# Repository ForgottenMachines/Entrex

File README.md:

# Entrex
Entrex is an early 1970s data entry systems, designed to replace punchcard data entry into larger mainframe computers.

The technologies documented here will include all like-kind systems manufactured by Nixdorf, Redifon, ROCC & Mera, all originally designed by Entrex Inc, Burlington, MA USA.

See See http://entrex480.com for greater details.

Enjoy!

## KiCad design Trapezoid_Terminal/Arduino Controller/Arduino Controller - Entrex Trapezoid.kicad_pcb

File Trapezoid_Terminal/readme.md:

WARNING:  Until refined & corrected, Global Label tag arrows may not indicate the 
proper signal in/out direction.
IN was used as default when KiCad Symbols (components) were not clear on 
In vs Out signals, so always check component datasheets when in doubt.

Crude Schematic Intro/Training Video (with lots of chapters for skipping):
https://www.youtube.com/watch?v=paqGd3PHxyc

Terminal/System use overview:
https://entrex480.blogspot.com/2022/09/how-does-entrexnixdorf-trapezoid.html

TucsonTom Collaborator Commentary:
http://cholla.mmto.org/computers/reverse/entrex/

EPROM Reverse Engineering:
https://github.com/phar/nixdorf-6xx-project

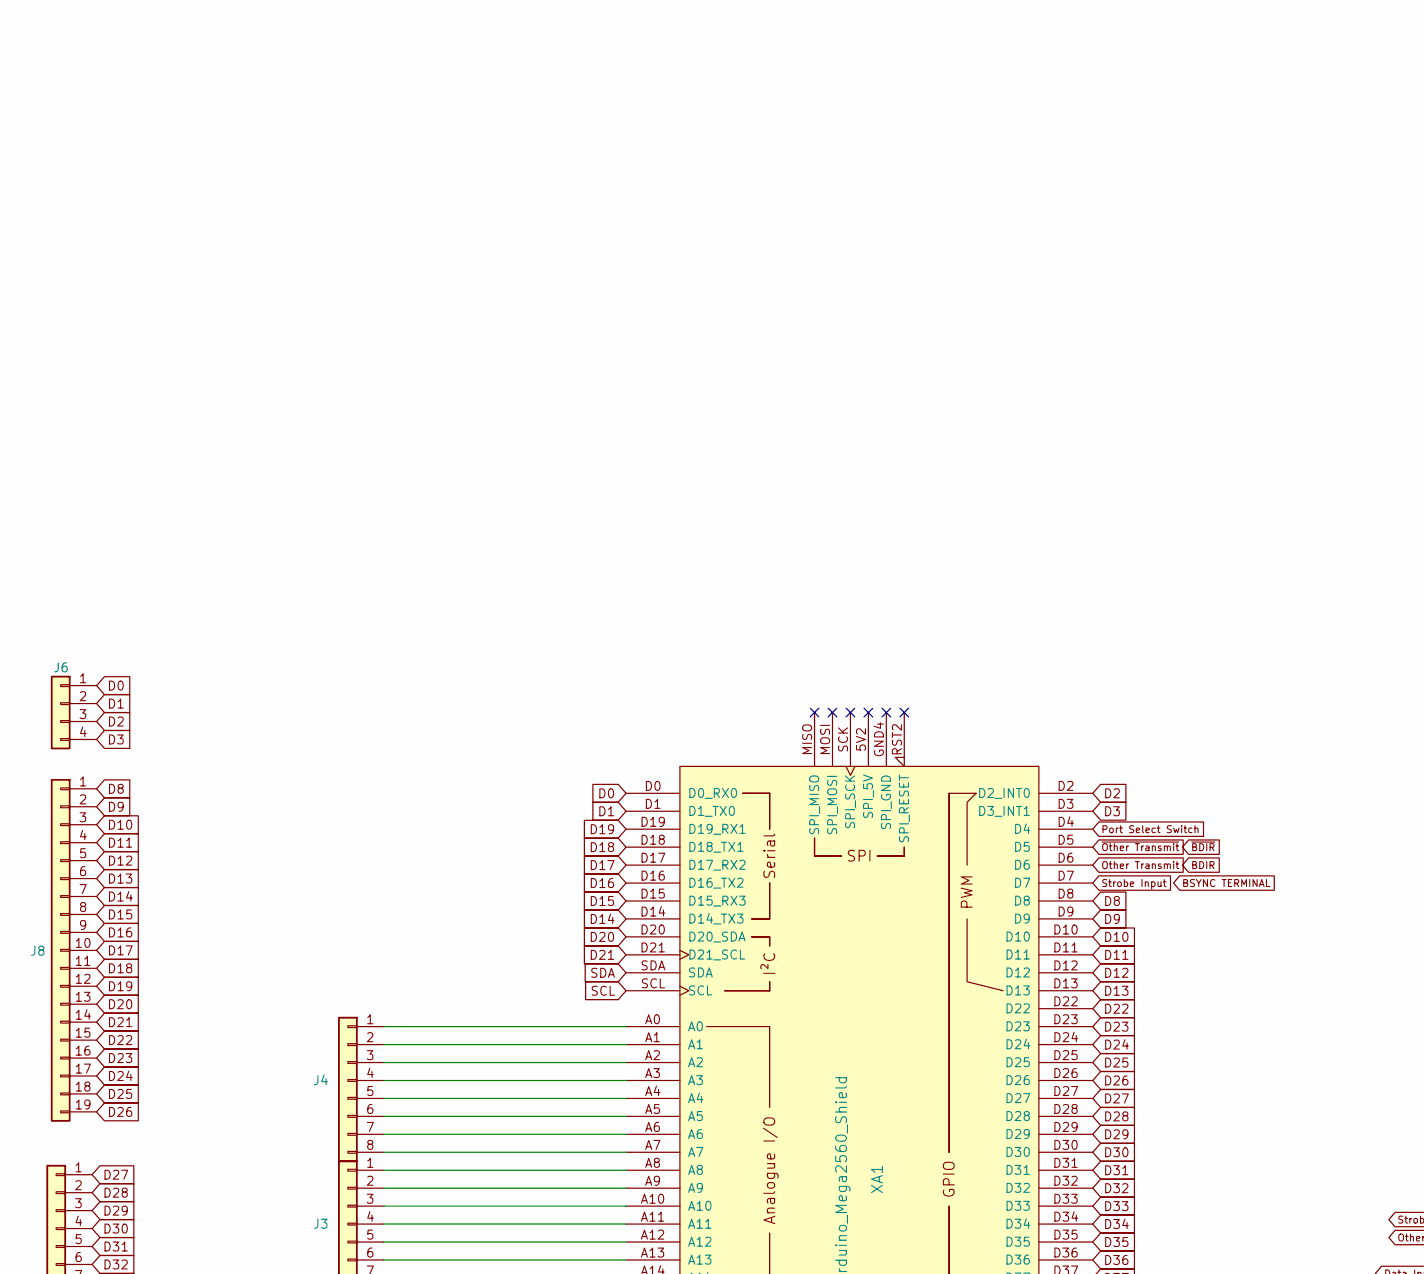
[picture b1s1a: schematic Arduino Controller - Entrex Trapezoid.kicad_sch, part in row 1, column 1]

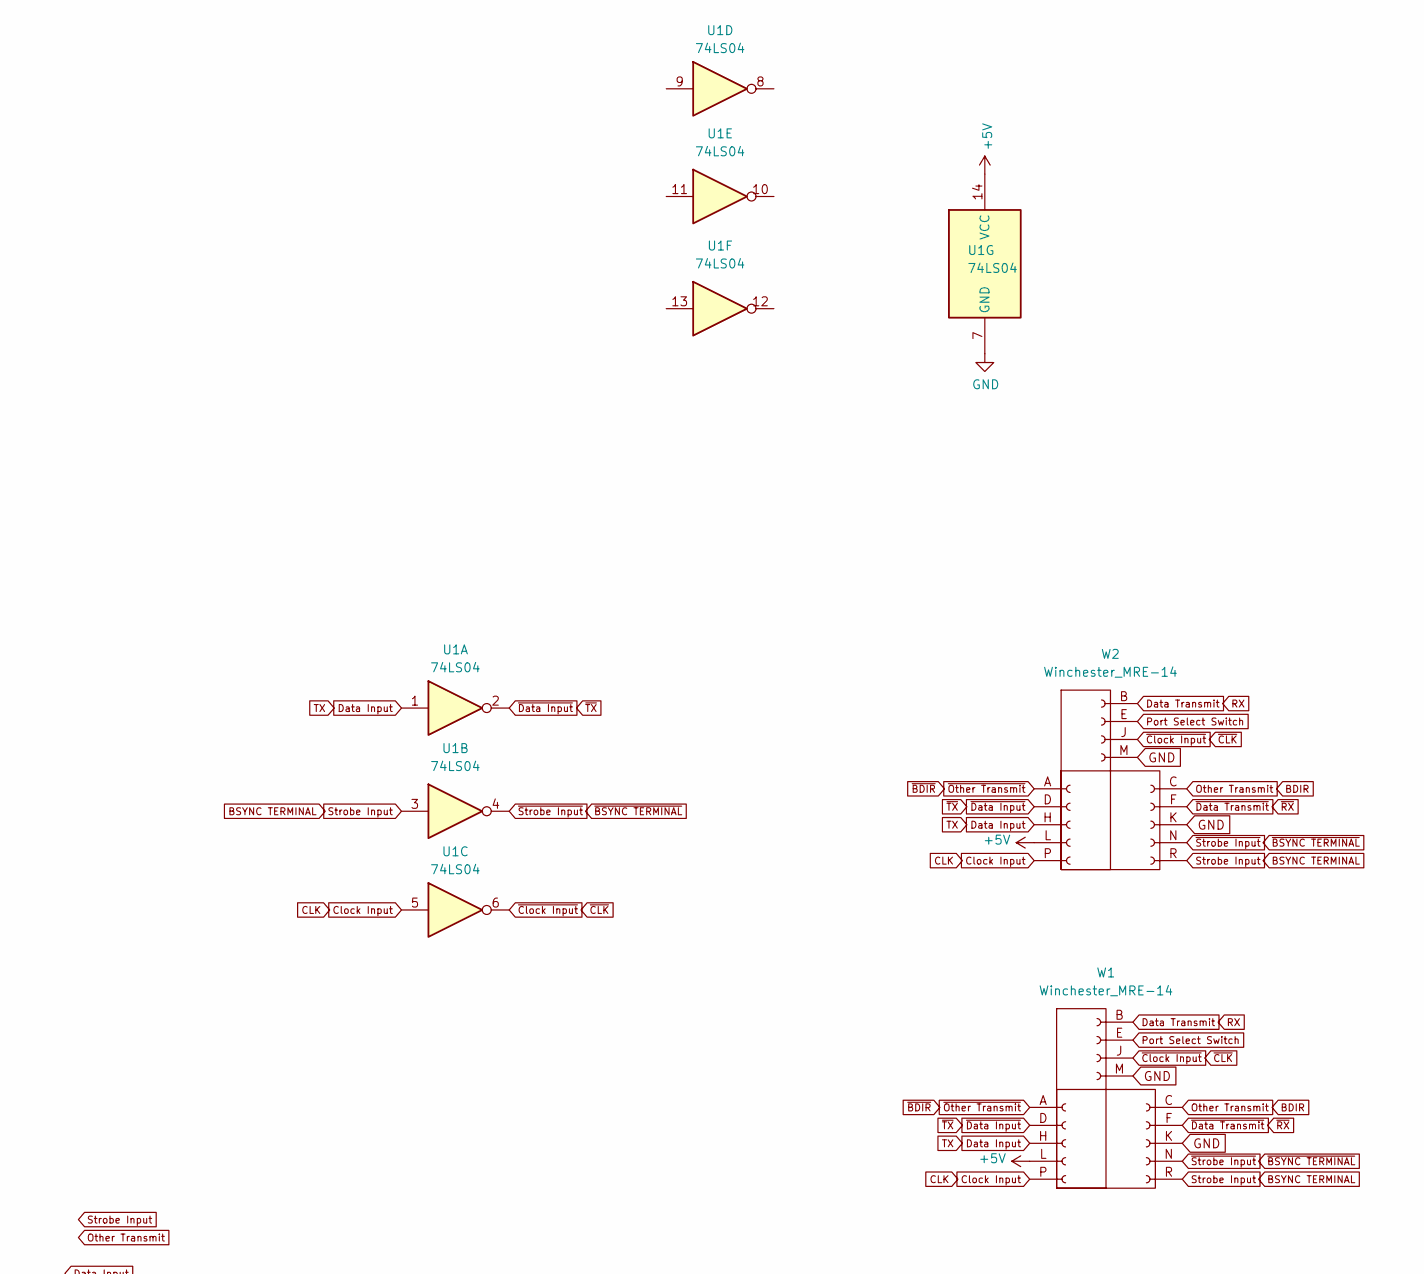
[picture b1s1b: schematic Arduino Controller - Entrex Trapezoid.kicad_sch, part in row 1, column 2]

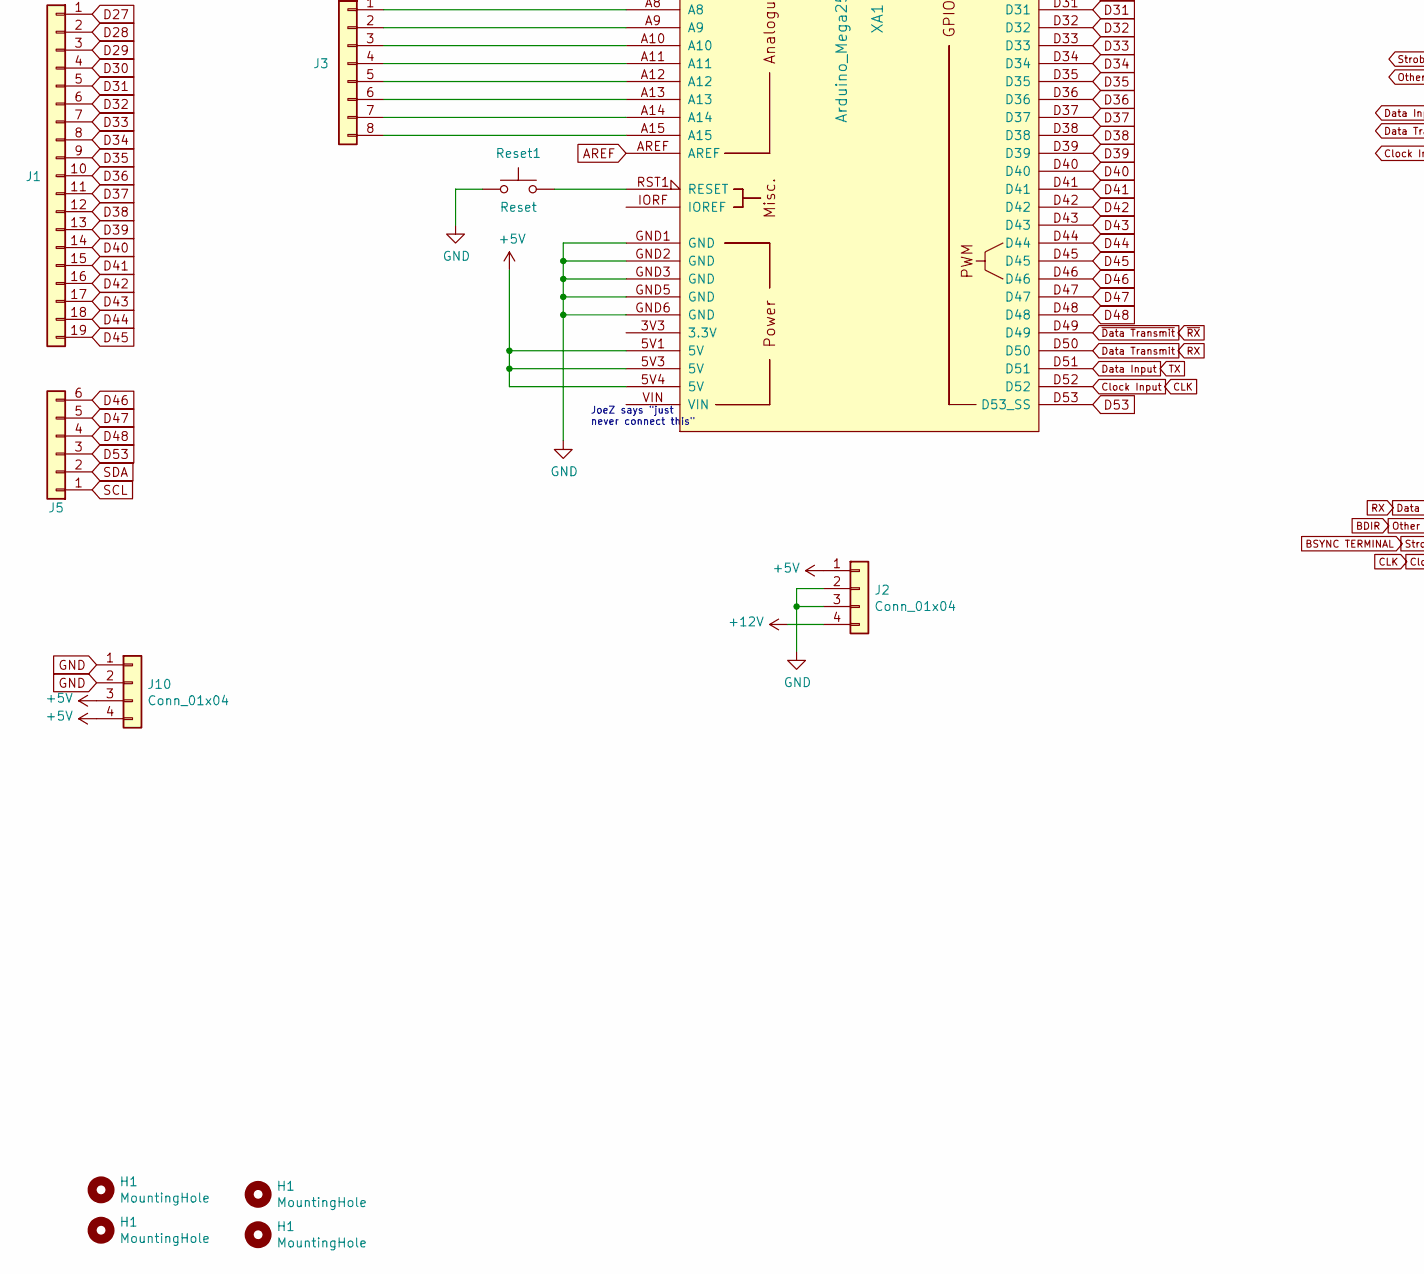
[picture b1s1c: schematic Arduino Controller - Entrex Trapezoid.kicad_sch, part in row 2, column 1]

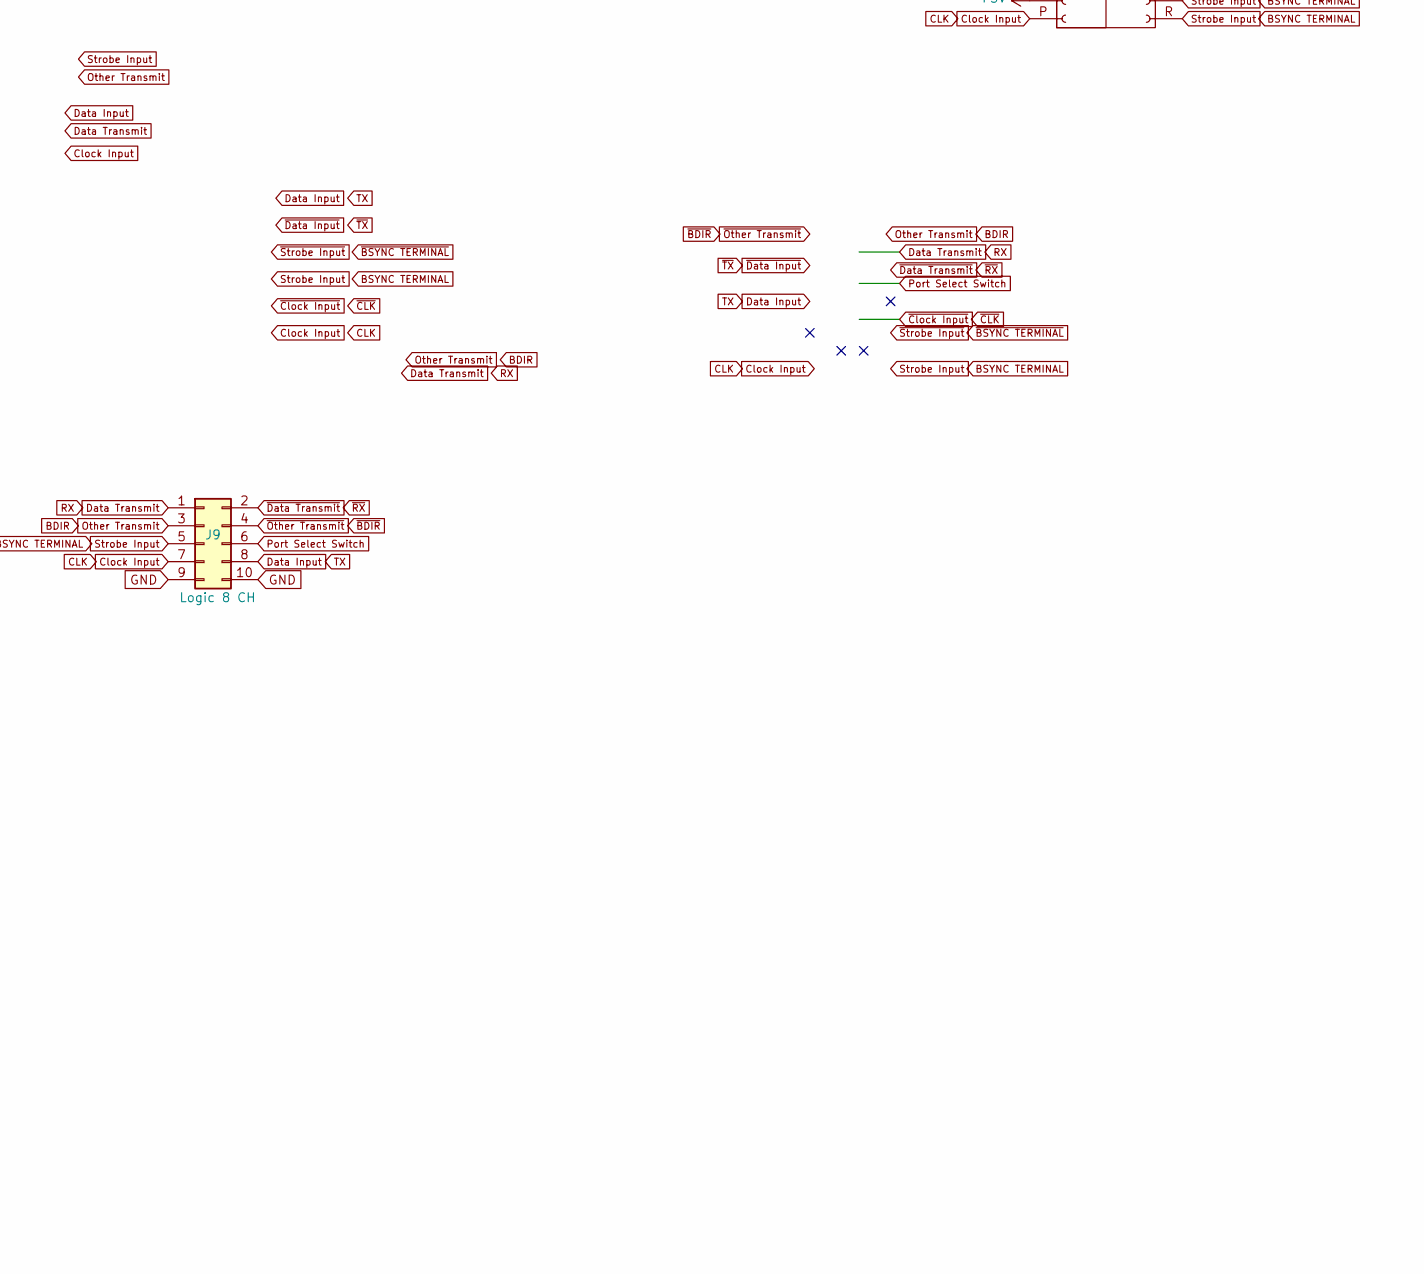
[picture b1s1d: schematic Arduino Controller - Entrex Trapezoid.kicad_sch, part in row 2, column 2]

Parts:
H1: MountingHole; MountingHole_3mm
J1, J8: Conn_01x19; PinHeader_1x19_P2.54mm_Vertical
J2, J6, J10: Conn_01x04; PinHeader_1x04_P2.54mm_Vertical
J3, J4: Conn_01x08; PinHeader_1x08_P2.54mm_Vertical
J5: Conn_01x06; PinHeader_1x06_P2.54mm_Vertical
J9: Logic 8 CH; PinHeader_2x05_P2.54mm_Vertical - Backside
Reset1: Reset; SW_PUSH_6mm
U1: 74LS04; DIP-14_W7.62mm
W1, W2: Winchester_MRE-14; Winchester MRE14 @ 2.54mm pitch
XA1: Arduino_Mega2560_Shield

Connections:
+5V: J2.1, J10.3, J10.4, U1.14 (VCC), W1.L (Pin_4), W2.L (Pin_4), XA1.5V1 (5V), XA1.5V3 (5V), XA1.5V4 (5V)
+12V: J2.4
AREF: XA1.AREF
Clock Input: J9.7, U1.5, W1.P (Pin_5), W2.P (Pin_5), XA1.D52
D0: J6.1, XA1.D0 (D0_RX0)
D1: J6.2, XA1.D1 (D1_TX0)
D2: J6.3, XA1.D2 (D2_INT0)
D3: J6.4, XA1.D3 (D3_INT1)
D8: J8.1, XA1.D8
D9: J8.2, XA1.D9
D10: J8.3, XA1.D10
D11: J8.4, XA1.D11
D12: J8.5, XA1.D12
D13: J8.6, XA1.D13
D14: J8.7, XA1.D14 (D14_TX3)
D15: J8.8, XA1.D15 (D15_RX3)
D16: J8.9, XA1.D16 (D16_TX2)
D17: J8.10, XA1.D17 (D17_RX2)
D18: J8.11, XA1.D18 (D18_TX1)
D19: J8.12, XA1.D19 (D19_RX1)
D20: J8.13, XA1.D20 (D20_SDA)
D21: J8.14, XA1.D21 (D21_SCL)
D22: J8.15, XA1.D22
D23: J8.16, XA1.D23
D24: J8.17, XA1.D24
D25: J8.18, XA1.D25
D26: J8.19, XA1.D26
D27: J1.1, XA1.D27
D28: J1.2, XA1.D28
D29: J1.3, XA1.D29
D30: J1.4, XA1.D30
D31: J1.5, XA1.D31
D32: J1.6, XA1.D32
D33: J1.7, XA1.D33
D34: J1.8, XA1.D34
D35: J1.9, XA1.D35
D36: J1.10, XA1.D36
D37: J1.11, XA1.D37
D38: J1.12, XA1.D38
D39: J1.13, XA1.D39
D40: J1.14, XA1.D40
D41: J1.15, XA1.D41
D42: J1.16, XA1.D42
D43: J1.17, XA1.D43
D44: J1.18, XA1.D44
D45: J1.19, XA1.D45
D46: J5.6, XA1.D46
D47: J5.5, XA1.D47
D48: J5.4, XA1.D48
D53: J5.3, XA1.D53 (D53_SS)
Data Input: J9.8, U1.1, W1.H (Pin_3), W2.H (Pin_3), XA1.D51
Data Transmit: J9.1, W1.B (Pin_4), W2.B (Pin_4), XA1.D50
GND: J2.2, J2.3, J9.9, J9.10, J10.1, J10.2, Reset1.1, U1.7 (GND), W1.K (Pin_3), W1.M (Pin_1), W2.K (Pin_3), W2.M (Pin_1), XA1.GND1 (GND), XA1.GND2 (GND), XA1.GND3 (GND), XA1.GND5 (GND), XA1.GND6 (GND)
unnamed: J3.1, XA1.A8
unnamed: J3.2, XA1.A9
unnamed: J3.3, XA1.A10
unnamed: J3.4, XA1.A11
unnamed: J3.5, XA1.A12
unnamed: J3.6, XA1.A13
unnamed: J3.7, XA1.A14
unnamed: J3.8, XA1.A15
unnamed: J4.1, XA1.A0
unnamed: J4.2, XA1.A1
unnamed: J4.3, XA1.A2
unnamed: J4.4, XA1.A3
unnamed: J4.5, XA1.A4
unnamed: J4.6, XA1.A5
unnamed: J4.7, XA1.A6
unnamed: J4.8, XA1.A7
unnamed: Reset1.2, XA1.RST1 (RESET)
Other Transmit: J9.3, W1.C (Pin_5), W2.C (Pin_5), XA1.D6
Port Select Switch: J9.6, W1.E (Pin_3), W2.E (Pin_3), XA1.D4
SCL: J5.1, XA1.SCL
SDA: J5.2, XA1.SDA
~Clock Input: U1.6, W1.J (Pin_2), W2.J (Pin_2)
~Data Input: U1.2, W1.D (Pin_2), W2.D (Pin_2)
~Data Transmit: J9.2, W1.F (Pin_4), W2.F (Pin_4), XA1.D49
~Other Transmit: J9.4, W1.A (Pin_1), W2.A (Pin_1), XA1.D5

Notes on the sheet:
JoeZ says "just never connect this"

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
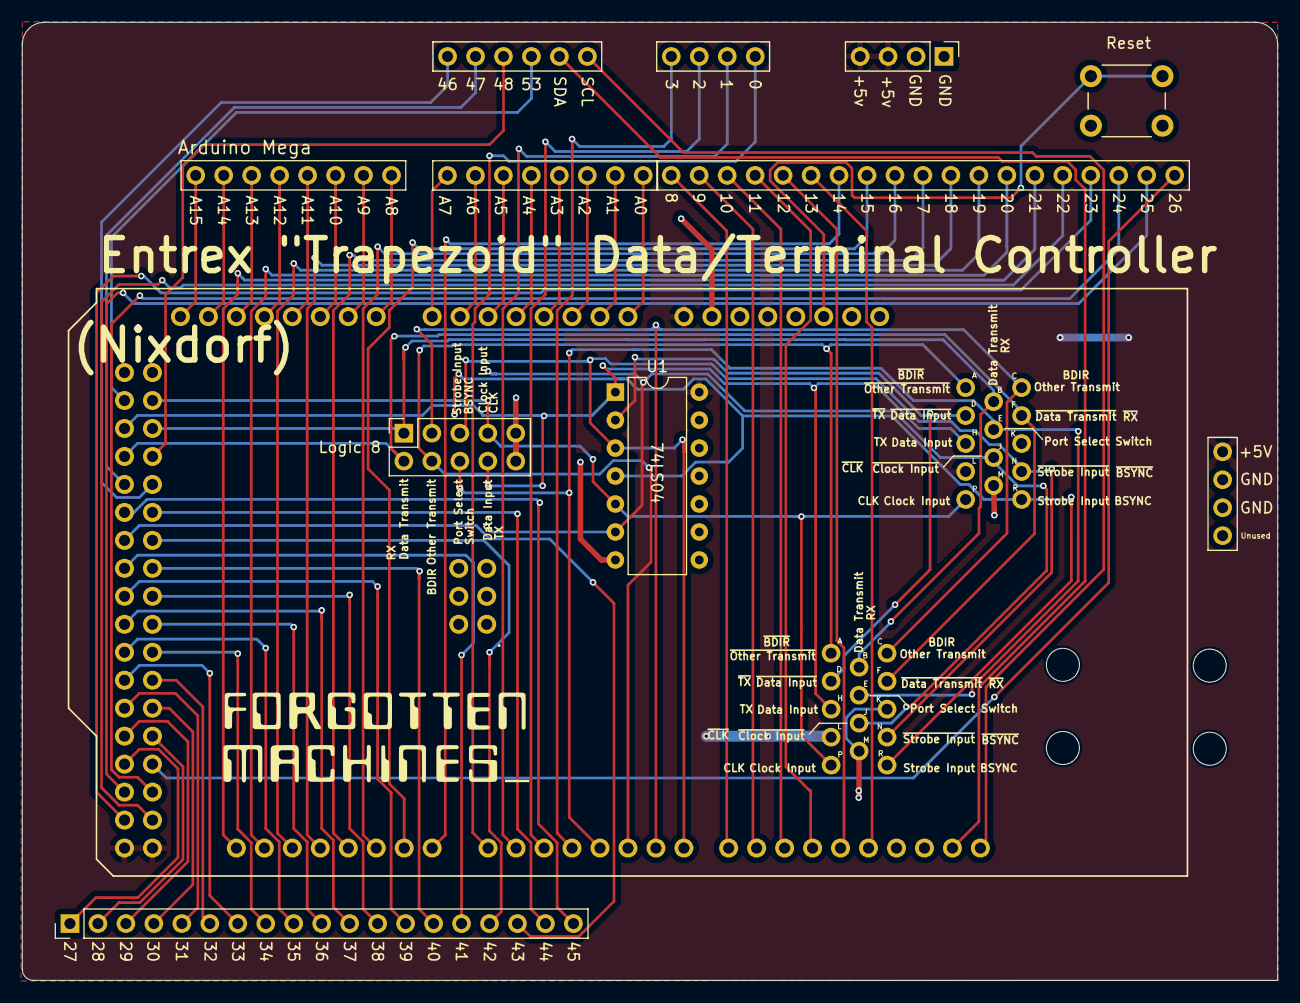
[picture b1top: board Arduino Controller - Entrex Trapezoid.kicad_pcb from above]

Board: 2 copper layers, 114.0 x 87.0 mm, 18 parts (0 on the bottom side), 78 nets.

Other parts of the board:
H2, H3, H4: MountingHole; MountingHole_3mm

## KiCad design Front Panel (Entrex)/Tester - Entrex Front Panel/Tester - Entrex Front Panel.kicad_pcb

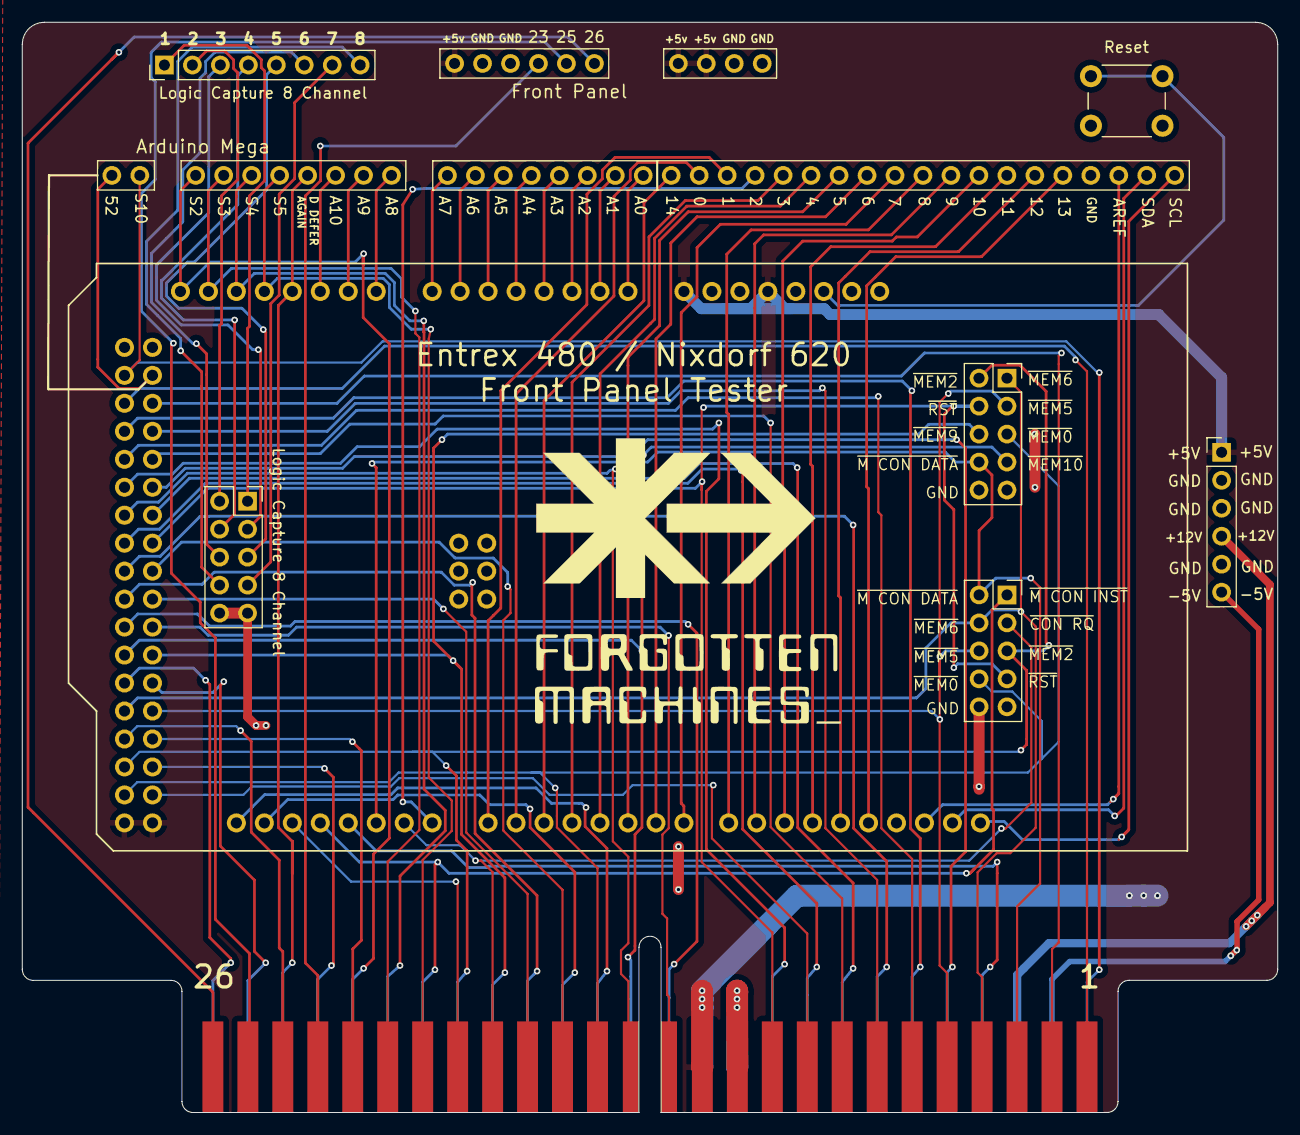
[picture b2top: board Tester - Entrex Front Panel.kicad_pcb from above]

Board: 2 copper layers, 114.0 x 99.0 mm, 14 parts (1 on the bottom side), 89 nets.

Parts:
J1: Logic 8 CH; PinHeader_1x08_P2.54mm_Vertical
J2: Conn_01x04; PinHeader_1x06_P2.54mm_Vertical
J3, J4: Conn_01x08; PinHeader_1x08_P2.54mm_Vertical
J5: Conn_01x06; PinHeader_1x06_P2.54mm_Vertical
J6: Conn_01x04; PinHeader_1x04_P2.54mm_Vertical
J7: Conn_01x02; PinHeader_1x02_P2.54mm_Vertical
J8: Conn_01x19; PinHeader_1x19_P2.54mm_Vertical
J9, J11, J12: Logic 8 CH; PinHeader_2x05_P2.54mm_Vertical - Backside
J10: Conn_02x26_Top_Bottom; DG Nova Front Panel Card Edge
SW1: Reset; SW_PUSH_6mm
XA1: Arduino_Mega2560_Shield

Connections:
52: J10.52, XA1.D31
64K: J10.42, XA1.D20 (D20_SDA)
+5V: J2.1, J5.6, J6.3, J6.4, J10.12, J10.38, XA1.5V1 (5V), XA1.5V3 (5V), XA1.5V4 (5V), XA1.VIN
+V LAMP: J2.4, J10.29
-5V: J2.6, J10.28
AREF: J8.17, XA1.AREF
D3: J8.5, XA1.D3 (D3_INT1)
D4: J8.6, XA1.D4
D5: J8.7, XA1.D5
D6: J8.8, XA1.D6
D7: J8.9, XA1.D7
D8: J8.10, XA1.D8
D9: J8.11, XA1.D9
D10: J8.12, XA1.D10
D11: J8.13, XA1.D11
D12: J8.14, XA1.D12
D13: J8.15, XA1.D13
D DEFER AGAIN: J3.4, J10.50, XA1.A11
DISK CS: J10.6, XA1.D47
EXT CS: J10.32, XA1.D49
GND: J2.2, J2.3, J2.5, J5.4, J5.5, J6.1, J6.2, J8.16, J9.9, J9.10, J10.11, J10.37, J11.9, J11.10, J12.9, J12.10, SW1.1, XA1.GND1 (GND), XA1.GND2 (GND), XA1.GND3 (GND), XA1.GND5 (GND), XA1.GND6 (GND)
Logic1: J1.1, J12.1
Logic2: J1.2, J12.2
Logic3: J1.3, J12.3
Logic4: J1.4, J12.4
Logic5: J1.5, J12.5
Logic6: J1.6, J12.6
Logic7: J1.7, J12.7
Logic8: J1.8, J12.8
unnamed: J3.1, XA1.A8
unnamed: J3.2, XA1.A9
unnamed: J3.3, XA1.A10
unnamed: J4.1, XA1.A0
unnamed: J4.2, XA1.A1
unnamed: J4.3, XA1.A2
unnamed: J4.4, XA1.A3
unnamed: J4.5, XA1.A4
unnamed: J4.6, XA1.A5
unnamed: J4.7, XA1.A6
unnamed: J4.8, XA1.A7
unnamed: J7.1, XA1.D52
unnamed: J8.1, XA1.D2 (D2_INT0)
unnamed: J8.2, XA1.D1 (D1_TX0)
unnamed: J8.3, XA1.D0 (D0_RX0)
unnamed: J8.4, XA1.D14 (D14_TX3)
unnamed: J5.3, J10.23
unnamed: J5.2, J10.25
unnamed: J5.1, J10.26
unnamed: SW1.2, XA1.RST1 (RESET)
S2: J3.8, J10.48, XA1.A15
S3: J3.7, J10.21, XA1.A14
S4: J3.6, J10.47, XA1.A13
S5: J3.5, J10.20, XA1.A12
S10: J7.2, J10.27, XA1.D53 (D53_SS)
SCL: J8.19, XA1.SCL
SDA: J8.18, XA1.SDA
SWITCHOVER POWER: J10.2, XA1.D50
TAPE CS: J10.7, XA1.D48
~64K: J10.41, XA1.D21 (D21_SCL)
~CON DATA: J10.30, XA1.D17 (D17_RX2)
~CON INST: J10.19, XA1.D19 (D19_RX1)
~CON RQ: J10.18, J11.3, XA1.D15 (D15_RX3)
~DCHP OUT: J10.14, XA1.D43
~DEFER: J10.35, XA1.D41
~DISK RDY: J10.8, XA1.D46
~M CON DATA: J9.8, J10.3, J11.2, XA1.D16 (D16_TX2)
~M CON INST: J10.46, J11.1, XA1.D18 (D18_TX1)
~MA LOAD: J10.34, XA1.D42
~MBO0: J10.9, XA1.D22
~MEM0: J9.5, J10.15, J11.8, XA1.D23
~MEM1: J10.49, XA1.D24
~MEM2: J9.2, J10.45, J11.5, XA1.D25
~MEM3: J10.22, XA1.D26
~MEM4: J10.24, XA1.D27
~MEM5: J9.3, J10.5, J11.6, XA1.D28
~MEM6: J9.1, J10.4, J11.4, XA1.D29
~MEM7: J10.51, XA1.D30
~MEM9: J9.6, J10.44, XA1.D32
~MEM10: J9.7, J10.40, XA1.D33
~MEM11: J10.13, XA1.D34
~MEM12: J10.39, XA1.D35
~MEM13: J10.17, XA1.D36
~MEM14: J10.43, XA1.D37
~MEM15: J10.16, XA1.D38
~NORMAL: J10.1, XA1.D51
~POWER FAIL: J10.31, XA1.D44
~RST: J9.4, J10.10, J11.7, XA1.D40
~RUN: J10.33, XA1.D39
~SCNR BUSY: J10.36, XA1.D45

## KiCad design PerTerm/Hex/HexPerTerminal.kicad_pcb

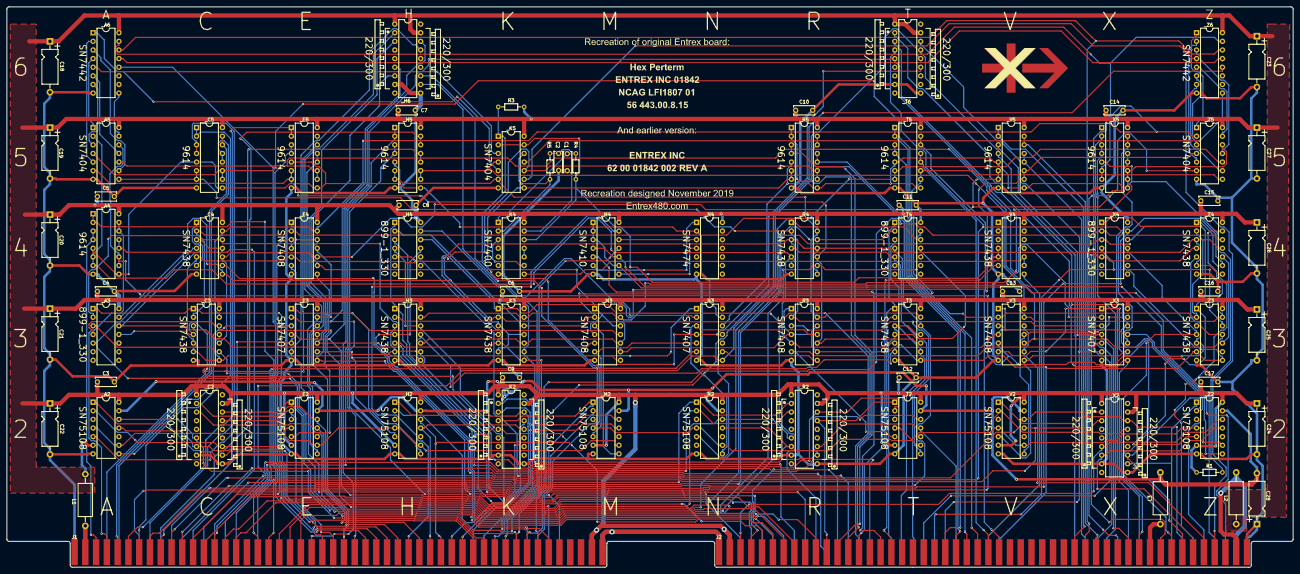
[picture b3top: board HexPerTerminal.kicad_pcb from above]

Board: 2 copper layers, 379.0 x 165.1 mm, 89 parts (0 on the bottom side), 194 nets.

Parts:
C1, C2: 470pF; C_Disc_D6.0mm_W2.5mm_P5.00mm
C3, C4, C5, C6, C7, C8, C9, C10, C11, C12, C13, C14, C15, C16, C17: 0.05uF; C_Disc_D6.0mm_W2.5mm_P5.00mm
C18, C19, C20, C21, C22, C23, C24, C25, C26, C27, C28: 6.8uF; CP_Axial_L10.0mm_D4.5mm_P15.00mm_Horizontal
G1: LOGO; logoFullN
G2: LOGO; logoXN
J1: portA; portA_NovaMod
J2: portB; portB_NovaMod
L1, L2, L3: 10uH; L_Axial_L9.5mm_D4.0mm_P15.24mm_Horizontal_Fastron_SMCC
R1, R3: 1K; R_Axial_DIN0204_L3.6mm_D1.6mm_P7.62mm_Horizontal
R4, R5: 220; R_Axial_DIN0204_L3.6mm_D1.6mm_P7.62mm_Horizontal
_A2: SN75108; DIP-14_W7.62mm
_A3: 899-1_330; DIP-14_W7.62mm
_A4: 9614; DIP-16_W7.62mm
_A5: SN7404; DIP-14_W7.62mm
_A6: SN7442; DIP-16_W7.62mm
_C2: 899-5_R220_R330; DIP-18_dualRnetwork
_C3, _C4: SN7438; DIP-14_W7.62mm
_C5: 9614; DIP-16_W7.62mm
_E2: SN75108; DIP-14_W7.62mm
_E3: SN7407; DIP-14_W7.62mm
_E4: SN7408; DIP-14_W7.62mm
_E5: 9614; DIP-16_W7.62mm
_H2: SN75108; DIP-14_W7.62mm
_H3: SN7438; DIP-14_W7.62mm
_H4: 899-1_330; DIP-14_W7.62mm
_H5: 9614; DIP-16_W7.62mm
_H6: 899-5_R220_R330; DIP-18_dualRnetwork
_K2: 899-5_R220_R330; DIP-18_dualRnetwork
_K3: SN7438; DIP-14_W7.62mm
_K4: SN7400; DIP-14_W7.62mm
_K5: SN7404; DIP-14_W7.62mm
_M2: SN75108; DIP-14_W7.62mm
_M3: SN7408; DIP-14_W7.62mm
_M4: SN7410; DIP-14_W7.62mm
_N2: SN75108; DIP-14_W7.62mm
_N3: SN7407; DIP-14_W7.62mm
_N4: SN7474; DIP-14_W7.62mm
_R2: 899-5_R220_R330; DIP-18_dualRnetwork
_R3: SN7408; DIP-14_W7.62mm
_R4: SN7438; DIP-14_W7.62mm
_R5: 9614; DIP-16_W7.62mm
_T2: SN75108; DIP-14_W7.62mm
_T3: SN7438; DIP-14_W7.62mm
_T4: 899-1_330; DIP-14_W7.62mm
_T5: 9614; DIP-16_W7.62mm
_T6: 899-5_R220_R330; DIP-18_dualRnetwork
_V2: SN75108; DIP-14_W7.62mm
_V3: SN7408; DIP-14_W7.62mm
_V4: SN7438; DIP-14_W7.62mm
_V5: 9614; DIP-16_W7.62mm
_X2: 899-5_R220_R330; DIP-18_dualRnetwork
_X3: SN7407; DIP-14_W7.62mm
_X4: 899-1_330; DIP-14_W7.62mm
_X5: 9614; DIP-16_W7.62mm
_Z2: SN75108; DIP-14_W7.62mm
_Z3, _Z4: SN7438; DIP-14_W7.62mm
_Z5: SN7404; DIP-14_W7.62mm
_Z6: SN7442; DIP-16_W7.62mm

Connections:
+5V: C3.1, C4.1, C5.1, C6.1, C7.1, C8.1, C9.1, C10.1, C11.1, C12.1, C13.1, C14.1, C15.1, C16.1, C17.1, C18.1, C19.1, C20.1, C21.1, C22.1, C23.1, C24.1, C25.1, C26.1, C27.1, J1.97, J1.98, J2.3, J2.4, L1.2, L2.2, R1.1, R3.2, _A2.6, _A2.14, _A4.16, _A5.14, _A6.16, _C2.14, _C3.14, _C4.14, _C5.16, _E2.6, _E2.14, _E3.14, _E4.14, _E5.16, _H2.6, _H2.14, _H3.14, _H5.16, _H6.14, _K2.14, _K3.14, _K4.14, _K5.14, _M2.6, _M2.14, _M3.14, _M4.14, _N2.6, _N2.14, _N3.14, _N4.14, _R2.14, _R3.14, _R4.14, _R5.16, _T2.6, _T2.14, _T3.14, _T5.16, _T6.14, _V2.6, _V2.14, _V3.14, _V4.14, _V5.16, _X2.14, _X3.14, _X5.16, _Z2.6, _Z2.14, _Z3.14, _Z4.14, _Z5.14, _Z6.16
-5V: C28.2, L3.2, _A2.13, _E2.13, _H2.13, _M2.13, _N2.13, _T2.13, _V2.13, _Z2.13
/InputGates/InGateBlock1/OutCh1: _E2.8, _E3.13, _E4.11
/InputGates/InGateBlock1/OutCh2: _E2.5, _E3.11, _E4.8
/InputGates/InGateBlock1/OutCh3: _A2.8, _E3.3, _E4.3
/InputGates/InGateBlock1/OutCh4: _A2.5, _E3.5, _E4.6
/InputGates/InGateBlock1/OutDr: R3.1, _A2.4, _A2.9, _E2.4, _E2.9, _H2.4, _H2.9, _K5.1, _M2.4, _M2.9, _N2.4, _N2.9, _T2.4, _T2.9, _V2.4, _V2.9, _Z2.4, _Z2.9
/InputGates/InGateBlock2/OutCh1: _E3.1, _H2.8, _M3.11
/InputGates/InGateBlock2/OutCh2: _E3.9, _H2.5, _M3.8
/InputGates/InGateBlock2/OutCh3: _M2.8, _M3.3, _N3.1
/InputGates/InGateBlock2/OutCh4: _M2.5, _M3.6, _N3.5
/InputGates/InGateBlock3/OutCh1: _N2.8, _N3.3, _R3.11
/InputGates/InGateBlock3/OutCh2: _N2.5, _N3.9, _R3.8
/InputGates/InGateBlock3/OutCh3: _R3.3, _T2.8, _X3.3
/InputGates/InGateBlock3/OutCh4: _R3.6, _T2.5, _X3.5
/InputGates/InGateBlock4/OutCh1: _V2.8, _V3.11, _X3.13
/InputGates/InGateBlock4/OutCh2: _V2.5, _V3.8, _X3.9
/InputGates/InGateBlock4/OutCh3: _V3.3, _X3.11, _Z2.8
/InputGates/InGateBlock4/OutCh4: _V3.6, _X3.1, _Z2.5
/OutputDrives/DriversBlock1/InAdrv: R1.2, _N3.12, _R5.5, _R5.9, _T5.5, _T5.9, _V5.5, _V5.9, _X5.5, _X5.9
/OutputDrives/DriversBlock2/InAdrv: _A4.5, _A4.9, _C5.5, _C5.9, _E5.5, _E5.9, _H5.5, _H5.9, _N3.13, _N4.2, _N4.6
A3: J1.3, J1.4, L1.1
A5: J1.5, _A4.3, _A4.4
A7: J1.7, _A4.14, _A4.15
A8: J1.8, _E5.14, _E5.15
A9: J1.9, _C5.14, _C5.15
A10: J1.10, _C5.12, _C5.13
A11: J1.11, _E5.1, _E5.2
A13: J1.13, _C5.1, _C5.2
A14: J1.14, _X4.13, _Z4.9
A15: J1.15, _V2.2, _X2.12
A16: J1.16, _C5.3, _C5.4
A17: J1.17, _H5.14, _H5.15
A18: J1.18, _H5.12, _H5.13
A19: J1.19, _T6.3, _X3.10
A20: J1.20, _T3.12, _T4.4
A21: J1.21, _R4.12, _T4.2
A22: J1.22, _N2.2, _R2.2
A23: J1.23, _E5.3, _E5.4
A24: J1.24, _A4.12, _A4.13
A25: J1.25, _X4.3, _Z3.9
A26: J1.26, _N2.1, _R2.1
A27: J1.27, _N3.8, _T6.11
A28: J1.28, _V2.12, _X2.1
A29: J1.29, _N2.12, _R2.5
A30: J1.30, _R2.13, _T2.2
A31: J1.31, _R4.9, _T4.13
A32: J1.32, _H5.1, _H5.2
A35: J1.35, _N3.4, _T6.10
A36: J1.36, _V2.11, _X2.2
A37: J1.37, _A4.1, _A4.2
A39: J1.39, _R4.1, _T4.12
A41: J1.41, _N2.11, _R2.6
A43: J1.43, _X4.2, _Z4.12
A45: J1.45, _T6.4, _X3.2
A47: J1.47, _C2.12, _E2.2
A49: J1.49, _C2.13, _E2.1
A51: J1.51, _E5.12, _E5.13
A53: J1.53, _H5.3, _H5.4
A55: J1.55, _A6.12
A57: J1.57, _A2.2, _C2.9
A59: J1.59, _A2.1, _C2.8
A61: J1.61, _C2.1, _E2.12
A63: J1.63, _M4.13
A65: J1.65, _C2.2, _E2.11
A67: J1.67, _H2.11, _K2.11
A69: J1.69, _H2.12, _K2.10
A71: J1.71, _H2.2, _K2.12
A73: J1.73, _H2.1, _K2.13
A75: J1.75, _A2.11, _C2.6
A76: J1.76, _K2.2, _M2.11
A77: J1.77, _A2.12, _C2.5
A78: J1.78, _K2.1, _M2.12
A79: J1.79, _M4.11
A81: J1.81, _C4.3, _C4.6, _C4.8, _C4.11, _K3.3, _K3.6, _K3.8, _K3.11, _R4.3, _R4.6, _R4.8, _R4.11, _Z4.3, _Z4.6, _Z4.8, _Z4.11
A83: J1.83, _Z6.12
A84: J1.84, _E3.12, _H6.1
A85: J1.85, _K2.4, _M2.2
A86: J1.86, _E3.10, _H6.2
A87: J1.87, _K2.3, _M2.1
A88: J1.88, _H6.9, _N3.6
A89: J1.89, _H6.8, _N3.2
A90: J1.90, _E3.4, _H6.13
A92: J1.92, _E3.6, _H6.12
B5: J2.5, _X2.5, _Z2.12
B6: J2.6, _E3.8, _H6.6
B7: J2.7, _R2.8, _T2.12
B8: J2.8, _E3.2, _H6.5
B9: J2.9, _A3.1, _C3.1
B10: J2.10, _A3.11, _C3.4
B11: J2.11, _H3.1, _H4.1
B12: J2.12, _H3.4, _H4.11
B13: J2.13, _A3.4, _C3.12
B14: J2.14, _A3.3, _C3.9
B15: J2.15, _H3.12, _H4.4
B16: J2.16, _H3.9, _H4.3
B18: J2.18, _A3.12, _C4.1
B19: J2.19, _A3.5, _C4.4
B20: J2.20, _H4.12, _K3.1
B21: J2.21, _R2.12, _T2.1
B22: J2.22, _H4.5, _K3.4
B23: J2.23, _R5.3, _R5.4
B24: J2.24, _A3.2, _C4.12
B25: J2.25, _R5.1, _R5.2
B26: J2.26, _A3.13, _C4.9
B27: J2.27, _V4.6
B28: J2.28, _H4.2, _K3.12
B30: J2.30, _H4.13, _K3.9
B31: J2.31, _M4.5
B33: J2.33, _T3.1, _T4.1
B34: J2.34, _T3.4, _T4.11
B36: J2.36, _T3.9, _T4.3
B38: J2.38, _R4.4, _T4.5
B40: J2.40, _A6.15, _Z6.15
B42: J2.42, _X4.4, _Z3.12
B43: J2.43, _R5.12, _R5.13
B44: J2.44, _T6.13, _X3.6
B45: J2.45, _R5.14, _R5.15
B46: J2.46, _R2.9, _T2.11
B47: J2.47, _T5.3, _T5.4
B49: J2.49, _T5.1, _T5.2
B51: J2.51, _T5.12, _T5.13
B52: J2.52, _V4.8
B53: J2.53, _T5.14, _T5.15
B54: J2.54, _C3.3, _C3.6, _C3.8, _C3.11, _H3.3, _H3.6, _H3.8, _H3.11, _T3.3, _T3.6, _T3.8, _T3.11, _Z3.3, _Z3.6, _Z3.8, _Z3.11
B67: J2.67, _V5.1, _V5.2
B68: J2.68, _V5.3, _V5.4
B69: J2.69, _A6.14, _Z6.14
B70: J2.70, _V5.12, _V5.13
B71: J2.71, _V5.14, _V5.15
B72: J2.72, _X5.1, _X5.2
B74: J2.74, _X5.3, _X5.4
B76: J2.76, _X5.12, _X5.13
B77: J2.77, _T6.12, _X3.4
B78: J2.78, _X5.14, _X5.15
B79: J2.79, _X4.11, _Z3.4
B80: J2.80, _T6.2, _X3.8
B81: J2.81, L3.1
B83: J2.83, _X4.5, _Z4.4
B85: J2.85, _X4.1, _Z3.1
B86: J2.86, _X2.8, _Z2.1
B87: J2.87, _X2.9, _Z2.2
B88: J2.88, _V2.1, _X2.13
B89: J2.89, _X2.6, _Z2.11
B90: J2.90, _X4.12, _Z4.1
B91: J2.91, _E4.1, _E4.4, _E4.9, _E4.12, _M3.1, _M3.4, _M3.9, _M3.12, _R3.1, _R3.4, _R3.9, _R3.12, _V3.1, _V3.4, _V3.9, _V3.12
B92: J2.92, _T6.1, _X3.12
B93: J2.93, _A6.13, _Z6.13
B94: J2.94, _M4.1, _M4.2, _M4.3, _M4.9
B96: J2.96, _M4.4, _M4.10
B97: J2.97, J2.98, L2.1
GNDD: C1.2, C2.1, C3.2, C4.2, C5.2, C6.2, C7.2, C8.2, C9.2, C10.2, C11.2, C12.2, C13.2, C14.2, C15.2, C16.2, C17.2, C18.2, C19.2, C20.2, C21.2, C22.2, C23.2, C24.2, C25.2, C26.2, C27.2, C28.1, J1.1, J1.2, J1.99, J1.100, J2.1, J2.2, J2.99, J2.100, _A2.7, _A3.14, _A4.8, _A5.7, _A6.8, _C2.7, _C3.7, _C4.7, _C5.8, _E2.7, _E3.7, _E4.7, _E5.8, _H2.7, _H3.7, _H4.14, _H5.8, _H6.7, _K2.7, _K3.7, _K4.7, _K5.7, _M2.7, _M3.7, _M4.7, _N2.7, _N3.7, _N4.7, _R2.7, _R3.7, _R4.7, _R5.8, _T2.7, _T3.7, _T4.14, _T5.8, _T6.7, _V2.7, _V3.7, _V4.7, _V5.8, _X2.7, _X3.7, _X4.14, _X5.8, _Z2.7, _Z3.7, _Z4.7, _Z5.7, _Z6.8
unnamed: C1.1, R5.2, _K4.13
unnamed: C2.2, R4.1, _K4.1
unnamed: R4.2, _K4.12, _K5.2, _K5.13, _V4.9, _V4.10
unnamed: R5.1, _K4.2, _K5.12
unnamed: _A5.1, _A6.4
unnamed: _A5.3, _A6.7
unnamed: _A5.5, _A6.2
unnamed: _A5.9, _A6.3
unnamed: _A5.11, _A6.6
unnamed: _A5.13, _A6.9
unnamed: _A6.1, _K5.5
unnamed: _A6.5, _K5.3
unnamed: _K4.3, _K4.9
unnamed: _K4.8, _V4.4, _V4.5
unnamed: _K4.10, _K4.11
unnamed: _K5.9, _Z6.4
unnamed: _K5.11, _Z6.9
unnamed: _M4.6, _N4.1
unnamed: _M4.8, _N4.4
unnamed: _M4.12, _N4.3
unnamed: _Z5.1, _Z6.1
unnamed: _Z5.3, _Z6.6
unnamed: _Z5.5, _Z6.2
unnamed: _Z5.9, _Z6.7
unnamed: _Z5.11, _Z6.3
unnamed: _Z5.13, _Z6.5
TermSel0: _C3.13, _C4.13, _E4.13, _X5.6, _X5.7, _Z5.2
TermSel1: _C3.10, _C4.10, _E4.10, _V5.6, _V5.7, _Z5.6
TermSel2: _C3.2, _C4.2, _E4.2, _T5.6, _T5.7, _Z5.10
TermSel3: _C3.5, _C4.5, _E4.5, _K5.8, _R5.6, _R5.7
TermSel4: _H3.13, _K3.13, _M3.13, _X5.10, _X5.11, _Z5.12
TermSel5: _H3.10, _K3.10, _M3.10, _V5.10, _V5.11, _Z5.4
TermSel6: _H3.2, _K3.2, _M3.2, _T5.10, _T5.11, _Z5.8
TermSel7: _H3.5, _K3.5, _K5.10, _M3.5, _R5.10, _R5.11
TermSel8: _H5.6, _H5.7, _K5.6, _R3.13, _R4.13, _T3.13
TermSel9: _A5.6, _E5.6, _E5.7, _R3.10, _R4.10, _T3.10
TermSel10: _A5.8, _C5.6, _C5.7, _R3.2, _R4.2, _T3.2
TermSel11: _A4.6, _A4.7, _A5.2, _R3.5, _R4.5, _T3.5
TermSel12: _H5.10, _H5.11, _K5.4, _V3.13, _Z3.13, _Z4.13
TermSel13: _A5.10, _E5.10, _E5.11, _V3.10, _Z3.10, _Z4.10
TermSel14: _A5.4, _C5.10, _C5.11, _V3.2, _Z3.2, _Z4.2
TermSel15: _A4.10, _A4.11, _A5.12, _V3.5, _Z3.5, _Z4.5

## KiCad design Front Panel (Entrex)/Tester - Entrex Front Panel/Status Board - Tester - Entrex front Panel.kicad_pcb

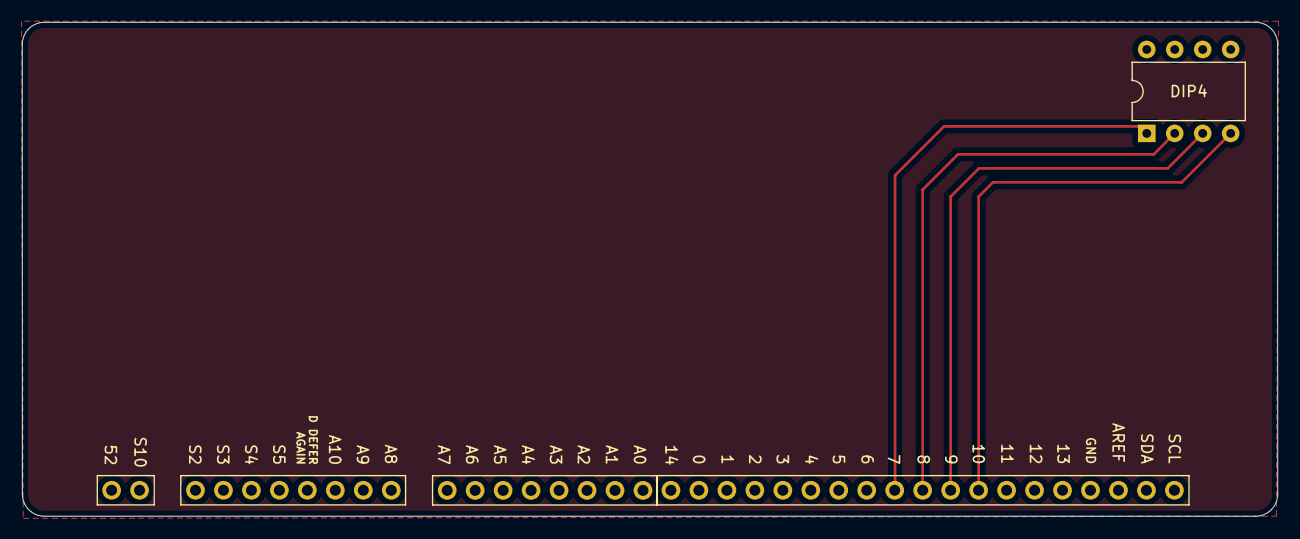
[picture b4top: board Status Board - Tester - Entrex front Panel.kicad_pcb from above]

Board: 2 copper layers, 114.0 x 44.9 mm, 5 parts (0 on the bottom side), 5 nets.

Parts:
DIP4: SW_DIP_x04; DIP-8_W7.62mm
J3, J4: Conn_01x08; PinHeader_1x08_P2.54mm_Vertical
J7: Conn_01x02; PinHeader_1x02_P2.54mm_Vertical
J8: Conn_01x19; PinHeader_1x19_P2.54mm_Vertical

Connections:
DIP1: DIP4.4, J8.12
DIP2: DIP4.3, J8.11
DIP3: DIP4.2, J8.10
DIP4: DIP4.1, J8.9
GND: DIP4.5, DIP4.6, DIP4.7, DIP4.8, J8.16
